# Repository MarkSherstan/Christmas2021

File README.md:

# Christmas 2021
Hardware and firmware project for the 2021 holiday season

# How to Use
1. Put 2x AAA batteries in holder on the back of ornament (place batteries with correct polarity or the board might catch on fire)
2. Press button to see 1 of 5 patterns

Other notes:
* This item 100% contains lead
* The batteries should last somewhere between one week and a year or two (multimeter was not accurate enough to get a real number but its been running for at least a week - update: 1+ year battery life has been reported)
* The board is not conformal coated meaning all contacts are "live". Therefore, make sure the board does not make contact with any metal objects (this will cause magic smoke; not good)
* Do your best to hold the PCB by the edges. This reduces the risk of static discharge which tends to put electrical components in the graveyard

# AS IS
THE SOFTWARE AND HARDWARE IS PROVIDED “AS IS”, WITHOUT WARRANTY OF ANY KIND, EXPRESS OR IMPLIED, INCLUDING BUT NOT LIMITED TO THE WARRANTIES OF MERCHANTABILITY, FITNESS FOR A PARTICULAR PURPOSE AND NONINFRINGEMENT. IN NO EVENT SHALL THE AUTHORS OR COPYRIGHT HOLDERS BE LIABLE FOR ANY CLAIM, DAMAGES OR OTHER LIABILITY, WHETHER IN AN ACTION OF CONTRACT, TORT OR OTHERWISE, ARISING FROM, OUT OF OR IN CONNECTION WITH THE SOFTWARE OR THE USE OR OTHER DEALINGS IN THE SOFTWARE.

# Software Requirements
Only required for changing design files
 
## Firmware
* Arduino IDE version 1.18.3 or greater
* In preferences add https://raw.githubusercontent.com/damellis/attiny/ide-1.6.x-boards-manager/package_damellis_attiny_index.json to `Additional Boards Manager URLs`
* Add ATtiny under `Boards Manager` and then configure the following settings:
- Board: ATtiny25/45/85
- Processor: ATtiny85
- Clock: Internal 8 MHz

Program over ICSP (will need a 2nd microcontroller acting as master)

## Hardware 
Boards designed in KiCad 5 and manufactured at JLCPCB

## Other
See all source code and design files at https://github.com/MarkSherstan/Christmas2021

# Future Ideas
- Double tap to keep pattern on

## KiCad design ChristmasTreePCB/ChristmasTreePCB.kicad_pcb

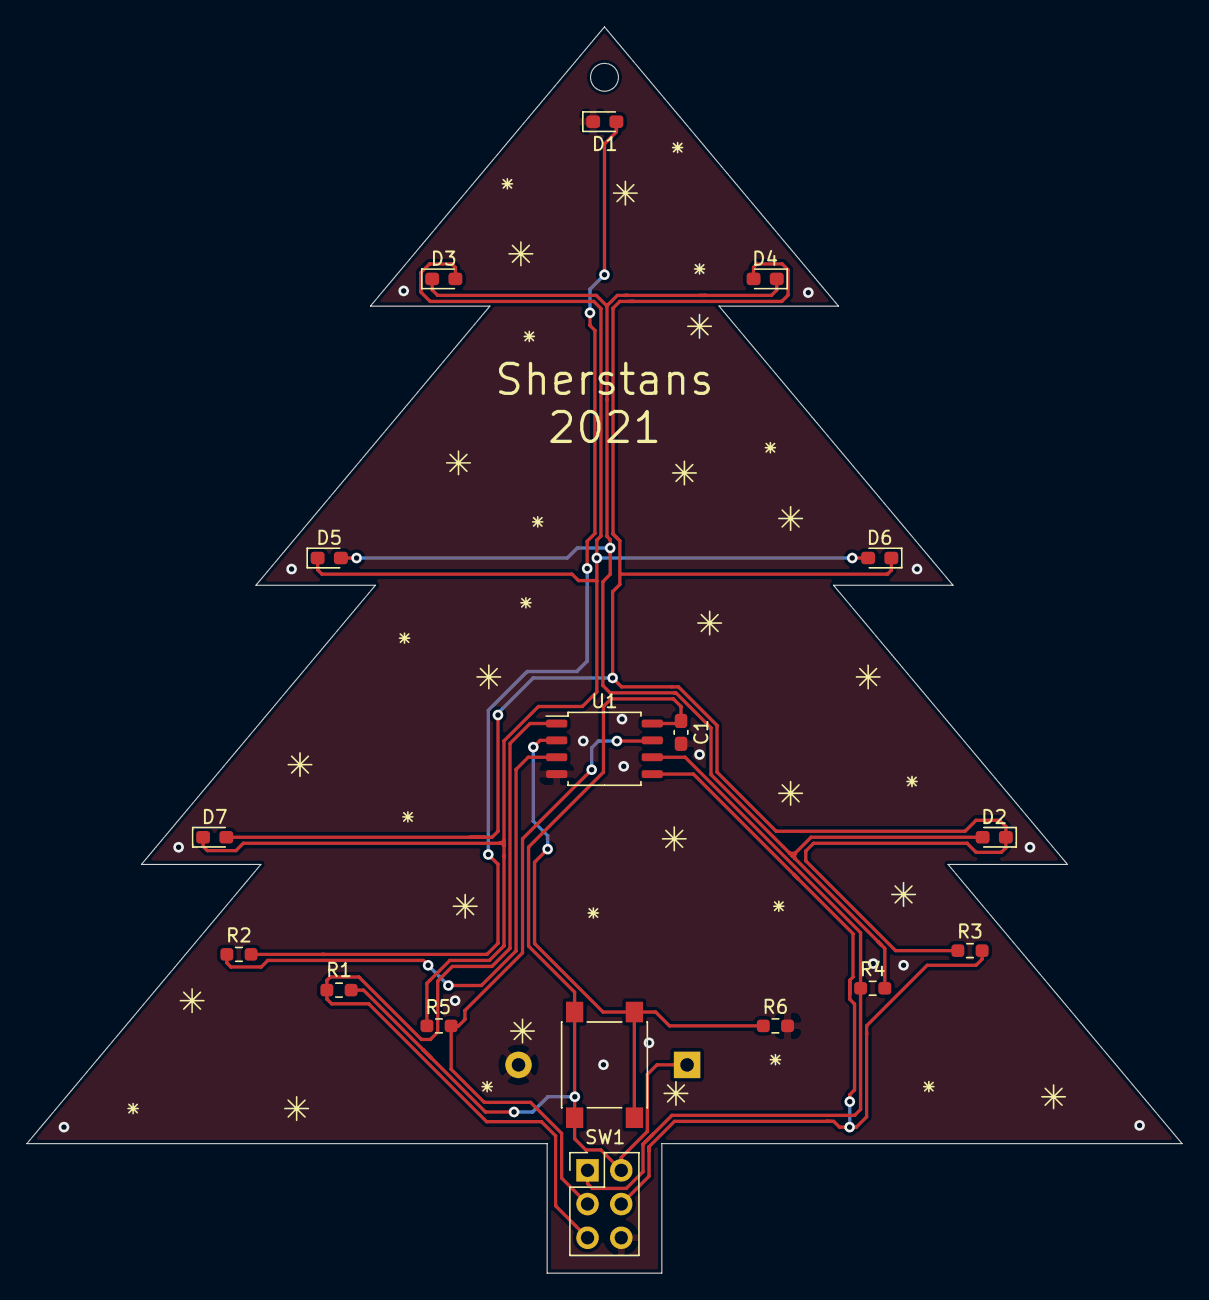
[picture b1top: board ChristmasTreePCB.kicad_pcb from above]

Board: 2 copper layers, 87.0 x 93.9 mm, 19 parts (1 on the bottom side), 12 nets.

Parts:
BT1: 2x AAA; 2468_Custom
C1: 0.1 uF X7R 20%; C_0603_1608Metric_Pad1.08x0.95mm_HandSolder
D1: Yellow 2.1V 20mA; LED_0603_1608Metric_Pad1.05x0.95mm_HandSolder
D2, D4, D5: Green 2V 20mA; LED_0603_1608Metric_Pad1.05x0.95mm_HandSolder
D3, D6, D7: Red 2V 20mA; LED_0603_1608Metric_Pad1.05x0.95mm_HandSolder
H1: M2; MountingHole_2.1mm
J1: ICSP; PinHeader_2x03_P2.54mm_Vertical
R1, R6: 10 kohm 5%; R_0603_1608Metric_Pad0.98x0.95mm_HandSolder
R2: 62 ohm 5%; R_0603_1608Metric_Pad0.98x0.95mm_HandSolder
R3, R4, R5: 33 ohm 5%; R_0603_1608Metric_Pad0.98x0.95mm_HandSolder
SW1: SPST-NO; SW_SPST_PTS645
U1: ATtiny85-20SHR; SOIC-8_5.275x5.275mm_P1.27mm

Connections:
GND: BT1.2, C1.1, D1.1, J1.6, R6.2, U1.4
unnamed: D1.2, R2.2
unnamed: D2.1, D4.2, D6.1, D7.2, R3.2
unnamed: D2.2, D3.1, D4.1, D5.2, R4.2
unnamed: D3.2, D5.1, D6.2, D7.1, R5.2
PB0-MOSI-RED: J1.4, R3.1, U1.5
PB1-MISO-GREEN: J1.1, R4.1, U1.6
PB2-SCK-DUAL: J1.3, R5.1, U1.7
PB4-WHITE: R2.1, U1.3
PCINT3: R6.1, SW1.2, U1.2
RESET: J1.5, R1.2, U1.1
VCC: BT1.1, C1.2, J1.2, R1.1, SW1.1, U1.8

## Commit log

2021-11-23 40% complete initial schematic
2021-11-23 Initial costing sheet
2021-11-23 Ignore some cache PCB files
2021-11-24 Add Charlieplexing for LEDs
2021-11-24 Schematic 95% done. Need to tidy and footprints
2021-11-25 Initial testing script
2021-11-25 Charlieplexing temp holder
2021-11-26 Update brain chip to be SOIC-8
2021-11-26 Update gitignore
2021-11-26 Project and board update
2021-11-26 Initial working example
2021-11-27 Working example for charlieplexing
2021-11-27 All footprints selected
2021-11-27 Rough layout
2021-11-27 50% complete routing
2021-11-28 roting complete
2021-11-28 Clean up routing
2021-11-28 Pre save before gerbers
2021-11-28 Gerbers
2021-11-28 Add resources directory
2021-11-28 Breadboard image
2021-11-30 Updated LED colors and R values. Made BOM
2021-11-30 Make PDF schematic
2021-11-30 Add .ds_store
2021-11-30 Define the initial sleep/wake functionality
2021-11-30 Setup charlieplexing
2021-11-30 Create first sequence and light reset function
2021-12-04 Fade the star
2021-12-04 Test on hardware
2021-12-04 Add .ino file
2021-12-04 Remove platformio files to keep it simple
2021-12-15 Initial commit light lib
2021-12-16 Quick README instructions
2021-12-16 Move all light refs to class
2021-12-16 Quick code tidy
2021-12-16 Pattern B
2021-12-16 Have different patterns
2021-12-18 lightSelect2x clean up function
2021-12-18 Around the world pattern C
2021-12-18 Pattern D: All lights stay on
2021-12-18 Documentation
2021-12-19 Pattern E: Zig zag
2021-12-20 Add patterns to main
2021-12-27 Swap D4 and D6 LED color
2021-12-27 Add progress pictures
2021-12-27 Update folder name
